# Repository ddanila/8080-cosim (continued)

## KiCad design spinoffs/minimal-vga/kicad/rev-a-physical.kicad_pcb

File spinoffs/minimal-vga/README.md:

# VJUGA minimal-VGA experiment

Status: **EXPERIMENTAL, WITH TWO PHYSICAL TRACKS**.

VJUGA explores a smaller +5 V, Z80-based board with socketed ROM, one 64 KiB
4164-style DRAM bank, keyboard I/O, and a VGA-oriented display path. It is an
independent experiment, not the main Juku replica and not a released hardware
product. The monolithic Rev A board remains on design hold. For modular Rev B,
the active order target is a complete five-board first article with VGA and TTL
serial; it remains on order hold while `docs/rev-b-five-board-order-plan.md` is
executed.

## Rev B modular status

[Rev B status](docs/rev-b-status.md) summarizes the five-card system and its
completed desk gates. The [five-board order plan](docs/rev-b-five-board-order-plan.md)
controls release. The [keyboard encoder pinout mismatch](docs/rev-b-io-parts.md#keyboard-pinout-mismatch--release-blocker)
requires correction and I/O package requalification before upload; physical
first-article acceptance remains pending. Use the
[current bench template](docs/rev-b-b1-bench-log.md) after the authorized order
arrives. Use only the exact five-archive candidate identified by the release
record; superseded packages must not be uploaded.

## Rev A monolithic status

### What works

- `sim/boot_check.sh` runs the patched Juku ROM on T80 in Z80 mode and
  compares the framebuffer with cosim after 6,000 video writes. This checks a
  bounded boot workload, not a complete banner, prompt or physical display.
- `sim/vjuga_boot_check.sh` runs the tv80 twin with the shared РУ5 DRAM,
  D6 decode-PROM and D8 pager models from `hdl/devices.v`, using the validated
  PROM tables. Both Mode B (D6 decode) and Mode A (U5's coarse A15/A14 decode)
  match the same bounded framebuffer oracle. This exercises the modeled
  memory path; it does not qualify socketed chips or prove detection of every
  chip fault. D8's output is unused and is not checked by this guard. Mode B
  uses D6 D0/pin12 as active-low `ROM_N`.
- The pinned T80 core also executes a built-in synthetic ROM (smoke test).
- The synthetic test exercises CPU ROM/RAM/I/O cycles, a bit-sliced DRAM
  model, independent refresh, video arbitration, keyboard-style input, and one
  VGA timing frame.
- An eight-instance logical HDL/KiCad model passes structural comparison.
- Nine structural HDL/board-JSON LVS slices pass with mutation controls,
  covering power/clock/reset, decode, CPU/ROM, DRAM bank and muxes, refresh,
  spare socket, timing and PPI. Whole-board coverage remains incomplete;
  these comparisons do not establish routed-copper continuity. See
  [LVS coverage](docs/rev-a-lvs-coverage.md) for exact counts and boundaries.
- U23 is retained only as an empty DNP spare socket. Its eight outputs have no
  consumers and the verified video timing/request handoff is U40/U41; generated
  assembly artifacts therefore omit U23 from owner IC insertion while still
  mounting its routed socket. Stage 7 LVS guards that exact socket topology.
- The Rev A physical source has 119 refs and 133 modeled nets, and now sockets
  the real Juku decode PROMs (U3 К556РТ4, U4 К155РЕ3) with a Mode-A/Mode-B
  jumper plus the Phase 4 observability headers (J96 clock-control, J97 high
  address + write strobe, J98 control bus); `check_rev_a_physical` enforces
  decode-socket and observability contracts that match the verified twin.
- **The framebuffer-readback boot oracle is built and validated.**
  `sim/vjuga_readback_check.sh` boots the twin with `+capture`, reassembles the
  write stream (`tools/vjuga_fb_readback/reassemble.py`), and confirms it equals
  both the twin's own dump and cosim's `vram.bin` at the selected write cutoff
  (default 6000). This validates bounded replay, not completion of the banner
  or physical capture reliability. Bench comparisons require matching ROM,
  cutoff and initial state; see [the procedure](docs/phase4-bench-bringup.md). A twin
  reference trace (`tools/vjuga_single_step/`) backs the UNO single-step rig.
- The committed four-layer routed PCB includes the Phase 3 decode sockets and
  observability headers and passes the repository's KiCad DRC and
  unconnected-item checks. Independent schematic/copper and power-return review
  still holds release.
- Any Rev A fabrication package predates both the U20/U21
  address-mux enable correction and the U22 refresh-counter cascade correction,
  and is **stale; do not upload or order it**. Do not confuse it with the separately
  validated Rev B packages under `fab/minimal-vga/revb/package/`. The Rev A upload ZIP is absent from the current workspace;
  [manufacturing readiness](docs/rev-a-manufacturing-readiness.md) owns its release gates.
  A fresh guarded stable-KiCad export and checksum are required.

### CPU and ROM

The Z80 supports the experiment's single +5 V supply. The adapted ROM replaces
three 8080 undocumented NOP opcodes and updates one checksum byte. The boot
gate compares original and patched 8080 framebuffers at its selected write
cutoff, then compares the T80 Z80 result; it does not prove every firmware
service equivalent. See [ROM images](roms/README.md) for the patches, hashes
and reproduction commands. T80 runs in Z80 mode (`Mode => 0`).

### What does not work yet

- The current Rev A copper includes the Phase 3 decode sockets and observability
  headers and passes zero-violation/zero-unconnected KiCad DRC. Its two inner
  layers are reserved for filled GND/VCC planes; independent review remains.
- The U5 decode is simulated in both jumper modes, and U24's DRAM
  timing/wait-state reference passes the slower vendored MK4564-12 limits at
  4 MHz. Neither GAL has been compiled/programmed or validated in hardware.
- The physical U20/U21 mux inputs have CPU A0–A7 and refresh-row outputs,
  without CPU-column or video-address paths. The runnable DRAM scaffold does
  not close that hardware gap; see [the chip map](docs/rev-a-chip-map.md#dram-and-arbitration).
- The VGA test proves timing activity, not a Juku banner or prompt sourced from
  shared DRAM.
- No independent end-to-end schematic/design review has released the copper.

Therefore the fabrication outputs are useful engineering artifacts, but the
board is **not authorized for vendor upload, order, or assembly**.

### Current scope

Included in the experiment:

- socketed DIP Z80, ROM, 8255, programmable logic, and eight 4164-compatible
  DRAM devices;
- +5 V input protection, clock/reset, debug headers, and diagnostics;
- keyboard matrix interface;
- shared CPU/refresh/video DRAM scaffold;
- VGA timing/debug header and pixel-serializer path.

Excluded from Rev A: FDC, external bus, tape/serial/network/mouse interfaces,
historical placement, and the original composite/RF chain.

## Evidence map

- `docs/workbench-plan.md`: the bench-fixture direction (test the real Juku
  РУ5/РТ4/РЕ3 parts) and the phased build plan.
- `docs/phase4-bench-bringup.md`: the detailed Phase 4 plan — pre-fab
  observability design-ins, analyzer channel maps, the framebuffer-readback
  boot oracle, the UNO single-step rig, and the assembly/chip-test ladder.
- `hdl/README.md`: exactly what the synthetic simulation proves.
- `docs/rev-a-chip-map.md`: current physical decomposition.
- `docs/rev-a-gal-equations.md`: unvalidated programmable-logic draft.
- `docs/rev-a-placement-rules.md`: placement policy.
- `docs/rev-a-power-budget.md`: conservative planning estimate.
- `docs/rev-a-sourcing-plan.md`: future sourcing/assembly policy; stock must be
  rechecked at order time.
- `docs/rev-a-drc-readiness.md`: current stable-KiCad full-DRC result
  bound to the exact source-board SHA; the former fabrication package is
  explicitly stale after the mux-enable and refresh-counter corrections.
- `docs/rev-a-lvs-coverage.md`: exact staged physical-LVS scope, negative
  control, and the groups still outside the whole-board comparison.
- `docs/rev-a-usb-c-candidate.md`: checksum- and geometry-guarded exact HRO
  TYPE-C-31-M-17/C283540 J3 candidate; order-time orientation/stock remains.
- `docs/rev-a-ptc-candidate.md`: checksum-, electrical-, topology-, and
  static-fit-guarded Bourns MF-RG300-0-14/C3761779 F1 candidate; thermal,
  stock, and first-article checks remain.
- `docs/rev-a-tvs-candidate.md`: checksum-, polarity-, topology-, geometry-,
  and routed-clearance-guarded Littelfuse P4KE6.8A-B/C1666224 D1 candidate;
  surge, stock, and first-article checks remain.
- `kicad/fab-notes.md`: routed/package facts and release blockers.
- `docs/rev-a-manufacturing-readiness.md`: top-level package/design status.
- `external/`: pinned-core and third-party design notes.

Generated reports under `fab/minimal-vga/` are ignored build artifacts. Their
individual `READY` labels mean the named mechanical/package check passed; they
do not override the top-level design hold.

## Checks

Run the current simulation and structural/physical checks:

```sh
spinoffs/minimal-vga/sim/check.sh
```

Run only the logical schematic/HDL comparison:

```sh
spinoffs/minimal-vga/sync/check.sh
```

Run the completed physical-board LVS stages:

```sh
spinoffs/minimal-vga/sync/rev_a_power_clock_reset_lvs.sh
spinoffs/minimal-vga/sync/rev_a_decode_lvs.sh
spinoffs/minimal-vga/sync/rev_a_cpu_rom_lvs.sh
spinoffs/minimal-vga/sync/rev_a_dram_bank_lvs.sh
spinoffs/minimal-vga/sync/rev_a_dram_mux_lvs.sh
spinoffs/minimal-vga/sync/rev_a_refresh_counter_lvs.sh
spinoffs/minimal-vga/sync/rev_a_spare_socket_lvs.sh
spinoffs/minimal-vga/sync/rev_a_dram_timing_lvs.sh
spinoffs/minimal-vga/sync/rev_a_ppi_lvs.sh
```

Regenerate fabrication review artifacts only after accepting that they remain
non-release outputs:

```sh
spinoffs/minimal-vga/kicad/export_fab.sh
```

## Rev A release gate

This gate applies to the monolithic Rev A bench fixture. The modular Rev B
order criteria are in the [five-board order plan](docs/rev-b-five-board-order-plan.md).

Established simulation evidence:

- `sim/boot_check.sh` matches the cosim framebuffer at 6000 video writes.
- `sim/vjuga_boot_check.sh` matches both jumper modes through the Rev A top
  using the РУ5 DRAM and РТ4 decode models; the instantiated РЕ3 output is
  unused and unchecked.
- Decode and U24 DRAM-timing equations are simulated; see
  `sim/u24_dram_timing_check.sh`.

VGA output is waived for Rev A's bench-fixture scope: the guarded framebuffer
capture is its bounded boot oracle for the РУ5/РТ4 memory path. РЕ3 testing
requires a separate output-table capture from the debug header, as described
in the [bench procedure](docs/phase4-bench-bringup.md). This waiver does not
apply to the five-board Rev B order target.

Before Rev A can become an order candidate:

1. Complete the physical DRAM addressing and resolve its scanout scope under
   [the manufacturing requirements](docs/rev-a-manufacturing-readiness.md#remaining-release-requirements).
2. Compile, program and review the equations on the exact chosen GAL22V10
   devices.
3. Validate DRAM, reset, clock, power, connector and socket pinouts against
   selected parts.
4. Obtain an independent schematic, copper, Gerber, drill and power-return
   review, plus full-board LVS or an explicit owner waiver naming that
   independent review as compensating evidence.
5. Regenerate all package artifacts after the design is frozen.

Until then, work on VJUGA must not distract from the main replica's P0 closure
items in the repository-root `PLAN.md`.

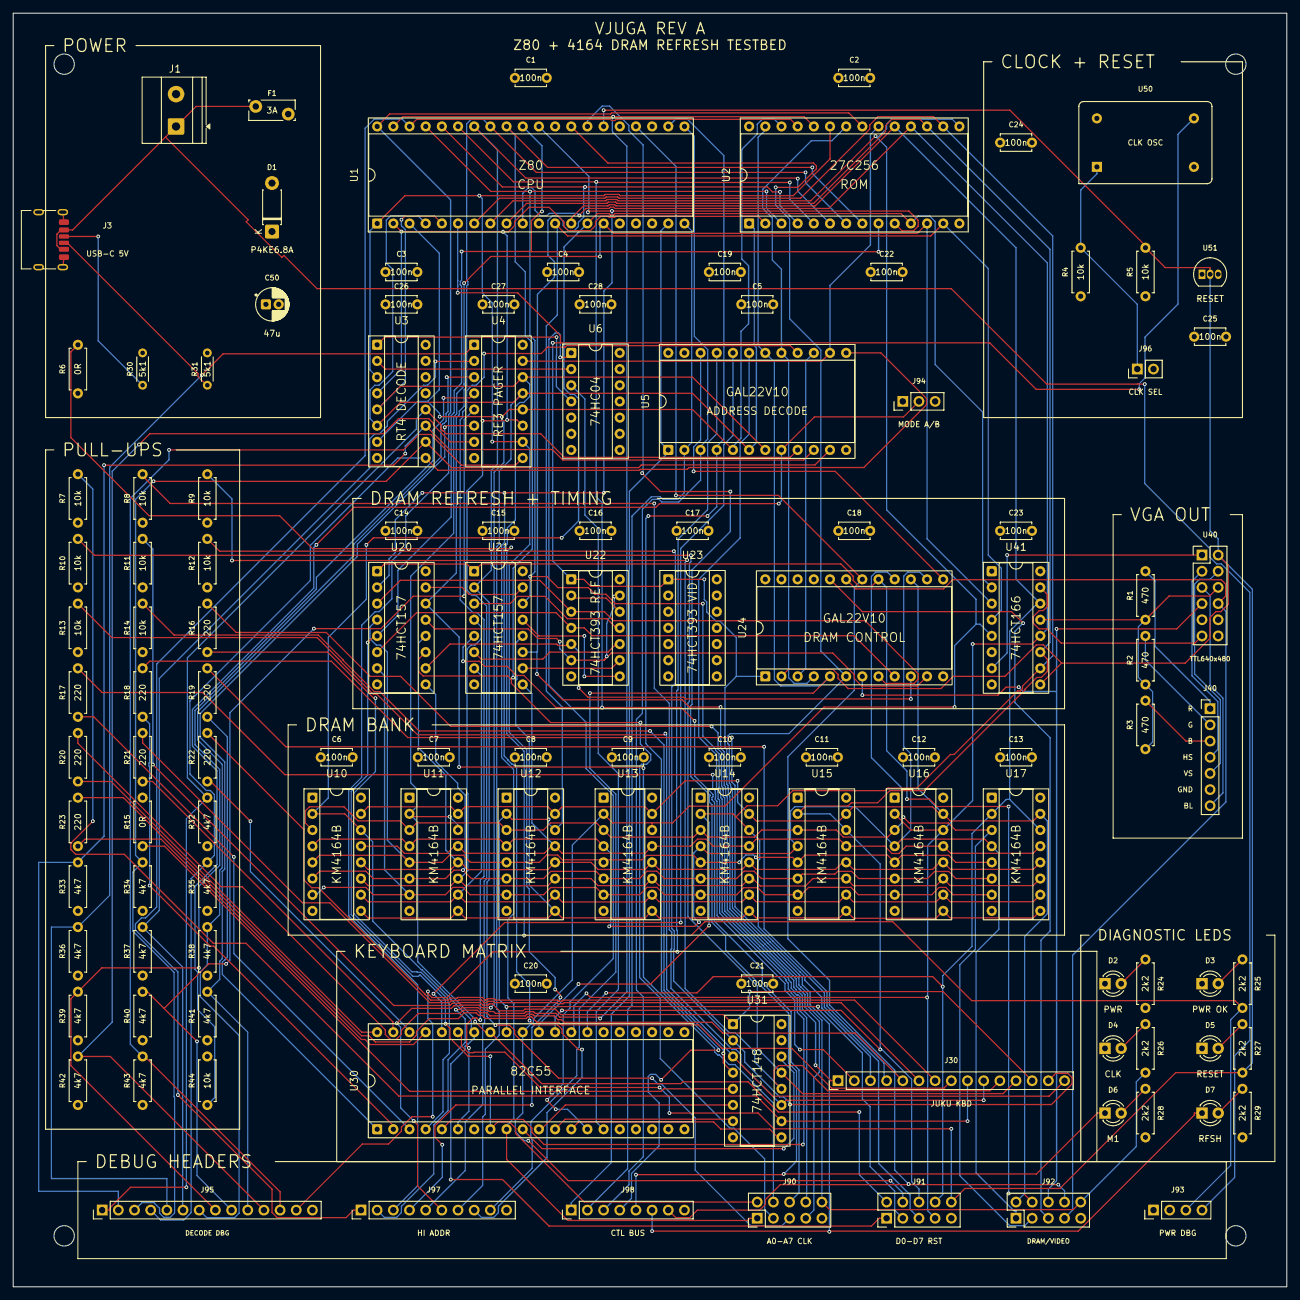
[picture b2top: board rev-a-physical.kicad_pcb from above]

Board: 4 copper layers, 200.0 x 200.0 mm, 119 parts (0 on the bottom side), 133 nets.

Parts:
C1, C2, C3, C4, C5, C6, C7, C8, C9, C10, C11, C12, C13, C14, C15, C16, C17, C18, C19, C20, C21, C22, C23, C24, C25, C26, C27, C28: 100n; C_Disc_D4.7mm_W2.5mm_P5.00mm
C50: 47u; CP_Radial_D5.0mm_P2.00mm
D1: P4KE6.8A; D_DO-41_SOD81_P7.62mm_Horizontal
D2: PWR; LED_D3.0mm
D3: PWR OK; LED_D3.0mm
D4: CLK; LED_D3.0mm
D5: RESET; LED_D3.0mm
D6: M1; LED_D3.0mm
D7: RFSH; LED_D3.0mm
F1: 3A; Fuse_Bourns_MF-RG300
J1: 5V_IN; TerminalBlock_Phoenix_MKDS-1,5-2-5.08_1x02_P5.08mm_Horizont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
J3: USB-C 5V; USB_C_Receptacle_HRO_TYPE-C-31-M-17
J30: JUKU KBD; PinHeader_1x15_P2.54mm_Vertical
J40: VGA_HEADER; PinHeader_1x07_P2.54mm_Vertical
J90: A0-A7 CLK; PinHeader_2x05_P2.54mm_Vertical
J91: D0-D7 RST; PinHeader_2x05_P2.54mm_Vertical
J92: DRAM/VIDEO; PinHeader_2x05_P2.54mm_Vertical
J93: PWR DBG; PinHeader_1x04_P2.54mm_Vertical
J94: MODE A/B; PinHeader_1x03_P2.54mm_Vertical
J95: DECODE DBG; PinHeader_1x14_P2.54mm_Vertical
J96: CLK SEL; PinHeader_1x02_P2.54mm_Vertical
J97: HI ADDR; PinHeader_1x10_P2.54mm_Vertical
J98: CTL BUS; PinHeader_1x08_P2.54mm_Vertical
R1, R2, R3: 470; R_Axial_DIN0207_L6.3mm_D2.5mm_P7.62mm_Horizontal
R4, R5, R7, R8, R9, R10, R11, R12, R13, R14, R44: 10k; R_Axial_DIN0207_L6.3mm_D2.5mm_P7.62mm_Horizontal
R6, R15: 0R; R_Axial_DIN0207_L6.3mm_D2.5mm_P7.62mm_Horizontal
R16, R17, R18, R19, R20, R21, R22, R23: 220; R_Axial_DIN0207_L6.3mm_D2.5mm_P7.62mm_Horizontal
R24, R25, R26, R27, R28, R29: 2k2; R_Axial_DIN0207_L6.3mm_D2.5mm_P7.62mm_Horizontal
R30, R31: 5k1; R_Axial_DIN0204_L3.6mm_D1.6mm_P5.08mm_Horizontal
R32, R33, R34, R35, R36, R37, R38, R39, R40, R41, R42, R43: 4k7; R_Axial_DIN0207_L6.3mm_D2.5mm_P7.62mm_Horizontal
U1: Z80; DIP-40_W15.24mm_Socket
U2: 27C256; DIP-28_W15.24mm_Socket
U3: RT4 DECODE; DIP-16_W7.62mm_Socket
U4: RE3 PAGER; DIP-16_W7.62mm_Socket
U5, U24: GAL22V10; DIP-24_W15.24mm_Socket
U6: 74HC04; DIP-14_W7.62mm_Socket
U10, U11, U12, U13, U14, U15, U16, U17: KM4164B; DIP-16_W7.62mm_Socket
U20, U21: 74HCT157; DIP-16_W7.62mm_Socket
U22: 74HCT393 REF; DIP-14_W7.62mm_Socket
U23: 74HCT393 VID; DIP-14_W7.62mm_Socket
U30: 82C55; DIP-40_W15.24mm_Socket
U31: 74HCT148; DIP-16_W7.62mm_Socket
U40: TTL640x480; PinHeader_2x06_P2.54mm_Vertical
U41: 74HCT166; DIP-16_W7.62mm_Socket
U50: CLK OSC; Oscillator_DIP-14
U51: RESET; TO-92_Inline

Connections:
A0: J90.1, U1.30, U2.10, U20.2, U30.9
A1: J90.2, U1.31, U2.9, U20.5, U30.8
A2: J90.3, U1.32, U2.8, U20.11
A3: J90.4, U1.33, U2.7, U20.14
A4: J90.5, U1.34, U2.6, U21.2
A5: J90.6, U1.35, U2.5, U21.5
A6: J90.7, U1.36, U2.4, U21.11
A7: J90.8, U1.37, U2.3, U21.14
A8: J97.1, U1.38, U2.25
A9: J97.2, U1.39, U2.24
A10: J97.3, U1.40, U2.21
A11: J97.4, U1.1, U2.23, U3.3, U4.10
A12: J97.5, U1.2, U2.2, U3.4, U4.11
A13: J97.6, U1.3, U2.26, U3.7, U4.12, U5.5
A14: J97.7, U1.4, U2.1, U3.6, U4.13, U5.6
A15: J97.8, U1.5, U3.5, U4.14, U5.7
ADDRMUX_SEL: J92.4, U20.1, U21.1, U24.17
BLANK_N: J40.7, U40.5
CAS_N: J92.2, U10.15, U11.15, U12.15, U13.15, U14.15, U15.15, U16.15, U17.15, U24.15
CLK: J90.10, J92.10, R26.1, U1.6, U22.1, U23.1, U24.1, U50.8
D0: J91.1, U1.14, U2.11, U10.2, U10.14, U30.34, U41.2
D1: J91.2, U1.15, U2.12, U11.2, U11.14, U30.33, U41.3
D2: J91.3, U1.12, U2.13, U12.2, U12.14, U30.32, U41.4
D3: J91.4, U1.8, U2.15, U13.2, U13.14, U30.31, U41.5
D4: J91.5, U1.7, U2.16, U14.2, U14.14, U30.30, U41.10
D5: J91.6, U1.9, U2.17, U15.2, U15.14, U30.29, U41.11
D6: J91.7, U1.10, U2.18, U16.2, U16.14, U30.28, U41.12
D7: J91.8, U1.13, U2.19, U17.2, U17.14, U30.27, U41.14
DECODE_WAIT_N: U5.22, U24.13
DEC_RAM_N: J95.2, R33.2, U3.11, U5.10
DEC_REV: J95.3, R34.2, U3.10, U5.11
DEC_ROE_N: J95.4, R35.2, U3.9, U5.13
DEC_ROM_N: J95.1, R32.2, U3.12, U5.9
DRAM_A0: U10.5, U11.5, U12.5, U13.5, U14.5, U15.5, U16.5, U17.5, U20.4
DRAM_A1: U10.7, U11.7, U12.7, U13.7, U14.7, U15.7, U16.7, U17.7, U20.7
DRAM_A2: U10.6, U11.6, U12.6, U13.6, U14.6, U15.6, U16.6, U17.6, U20.9
DRAM_A3: U10.12, U11.12, U12.12, U13.12, U14.12, U15.12, U16.12, U17.12, U20.12
DRAM_A4: U10.11, U11.11, U12.11, U13.11, U14.11, U15.11, U16.11, U17.11, U21.4
DRAM_A5: U10.10, U11.10, U12.10, U13.10, U14.10, U15.10, U16.10, U17.10, U21.7
DRAM_A6: U10.13, U11.13, U12.13, U13.13, U14.13, U15.13, U16.13, U17.13, U21.9
DRAM_A7: U10.9, U11.9, U12.9, U13.9, U14.9, U15.9, U16.9, U17.9, U21.12
DRAM_WE_N: J92.3, U10.3, U11.3, U12.3, U13.3, U14.3, U15.3, U16.3, U17.3, U24.16
GND: C1.2, C2.2, C3.2, C4.2, C5.2, C6.2, C7.2, C8.2, C9.2, C10.2, C11.2, C12.2, C13.2, C14.2, C15.2, C16.2, C17.2, C18.2, C19.2, C20.2, C21.2, C22.2, C23.2, C24.2, C25.2, C26.2, C27.2, C28.2, C50.2, D1.2, D2.1, D3.1, D4.1, D5.1, J1.2, J3.A12, J3.B12, J3.SH, J40.6, J90.9, J91.9, J92.9, J93.2, J94.3, J95.14, J96.2, J97.10, J98.8, R15.2, R30.2, R31.2, R44.2, U1.29, U2.14, U3.8, U3.13, U3.14, U3.15, U4.8, U5.12, U6.5, U6.7, U6.9, U6.11, U6.13, U10.16, U11.16, U12.16, U13.16, U14.16, U15.16, U16.16, U17.16, U20.8, U20.15, U21.8, U21.15, U22.2, U22.7, U22.12, U23.2, U23.7, U23.12, U23.13, U24.12, U30.7, U31.8, U40.10, U40.12, U41.1, U41.6, U41.8, U50.7, U51.1
HSYNC_N: J40.4, U40.3
IORQ_N: J98.2, U1.20, U5.2
IO_RD_N: U5.19, U30.5
IO_WR_N: U5.20, U30.36
KBD_COL0: J30.1, R16.2
KBD_COL0_DRV: R16.1, U30.4
KBD_COL1: J30.2, R17.2
KBD_COL1_DRV: R17.1, U30.3
KBD_COL2: J30.3, R18.2
KBD_COL2_DRV: R18.1, U30.2
KBD_COL3: J30.4, R19.2
KBD_COL3_DRV: R19.1, U30.1
KBD_COL4: J30.5, R20.2
KBD_COL4_DRV: R20.1, U30.40
KBD_COL5: J30.6, R21.2
KBD_COL5_DRV: R21.1, U30.39
KBD_COL6: J30.7, R22.2
KBD_COL6_DRV: R22.1, U30.38
KBD_COL7: J30.8, R23.2
KBD_COL7_DRV: R23.1, U30.37
KBD_EN_N: R15.1, U31.5
KBD_GS_N: U30.10, U31.14
KBD_ROW0_N: J30.9, R7.2, U31.10
KBD_ROW1_N: J30.10, R8.2, U31.11
KBD_ROW2_N: J30.11, R9.2, U31.12
KBD_ROW3_N: J30.12, R10.2, U31.13
KBD_ROW4_N: J30.13, R11.2, U31.1
KBD_ROW5_N: J30.14, R12.2, U31.2
KBD_ROW6_N: J30.15, R13.2, U31.3
KBD_ROW7_N: R14.2, U31.4
KBD_ROW_A0_N: U30.13, U31.9
KBD_ROW_A1_N: U30.12, U31.7
KBD_ROW_A2_N: U30.11, U31.6
LED_CLK_A: D4.2, R26.2
LED_M1_A: D6.2, R28.2
LED_PWR_A: D2.2, R24.2
LED_PWR_OK_A: D3.2, R25.2
LED_RESET_A: D5.2, R27.2
LED_RFSH_A: D7.2, R29.2
M1_N: D6.1, J98.5, U1.27
MEM_RD_N: U2.22, U5.17, U24.4
MEM_WR_N: J97.9, U2.27, U5.18, U24.5
MODE_B: J94.2, R44.1, U5.8
MREQ_N: J98.1, U1.19, U5.1
OSC_OE_N: J96.1, R4.2, U50.1
PC0: U6.1, U30.14
PC0_N: U3.2, U6.2
PC1: U6.3, U30.15
PC1_N: U3.1, U6.4
PIXCLK: U40.1, U41.7
PIXEL: R1.1, R2.1, R3.1, U40.6, U41.13
PIX_LOAD_N: U40.11, U41.15
PPI_CS_N: U5.16, U30.6
PWR_OK: J93.3, R6.2, R25.1
RAM_CE_N: U5.15, U24.3
RAS_N: J92.1, U10.4, U11.4, U12.4, U13.4, U14.4, U15.4, U16.4, U17.4, U24.14
RD_N: J98.3, U1.21, U5.3
RE3_D0: J95.5, R36.2, U4.1
RE3_D1: J95.6, R37.2, U4.2
RE3_D2: J95.7, R38.2, U4.3
RE3_D3: J95.8, R39.2, U4.4
RE3_D4: J95.9, R40.2, U4.5
RE3_D5: J95.10, R41.2, U4.6
RE3_D6: J95.11, R42.2, U4.7
RE3_D7: J95.12, R43.2, U4.9
REFRESH_ROW0: U20.3, U22.3, U24.8
REFRESH_ROW1: U20.6, U22.4, U24.9
REFRESH_ROW2: U20.10, U22.5, U24.10
REFRESH_ROW3: U20.13, U22.6, U22.13, U24.11
REFRESH_ROW4: U21.3, U22.11
REFRESH_ROW5: U21.6, U22.10
REFRESH_ROW6: U21.10, U22.9
REFRESH_ROW7: U21.13, U22.8
REFRESH_TICK: J92.5, U24.20
RESET_N: J91.10, R5.2, R27.1, U1.26, U24.2, U30.35, U40.2, U41.9, U51.2
REV_OUT: J95.13, U5.21
RFSH_N: D7.1, J98.6, U1.28, U24.6
ROM_CE_N: U2.20, U4.15, U5.14
USB_CC1: J3.A5, R30.1
USB_CC2: J3.B5, R31.1
VCC: C1.1, C2.1, C3.1, C4.1, C5.1, C6.1, C7.1, C8.1, C9.1, C10.1, C11.1, C12.1, C13.1, C14.1, C15.1, C16.1, C17.1, C18.1, C19.1, C20.1, C21.1, C22.1, C23.1, C24.1, C25.1, C26.1, C27.1, C28.1, C50.1, D1.1, F1.2, J93.1, J94.1, R4.1, R5.1, R6.1, R7.1, R8.1, R9.1, R10.1, R11.1, R12.1, R13.1, R14.1, R24.1, R28.1, R29.1, R32.1, R33.1, R34.1, R35.1, R36.1, R37.1, R38.1, R39.1, R40.1, R41.1, R42.1, R43.1, U1.11, U1.16, U1.17, U1.25, U2.28, U3.16, U4.16, U5.24, U6.14, U10.8, U11.8, U12.8, U13.8, U14.8, U15.8, U16.8, U17.8, U20.16, U21.16, U22.14, U23.14, U24.24, U30.26, U31.16, U40.9, U41.16, U50.14, U51.3
VCC_RAW: F1.1, J1.1, J3.A9, J3.B9, J93.4
VGA_B: J40.3, R3.2
VGA_G: J40.2, R2.2
VGA_R: J40.1, R1.2
VIDEO_ACK: J92.7, U24.19, U40.8
VIDEO_REQ: J92.6, U24.7, U40.7
VSYNC_N: J40.5, U40.4
WAIT_N: J92.8, J98.7, U1.24, U24.18
WR_N: J98.4, U1.22, U5.4

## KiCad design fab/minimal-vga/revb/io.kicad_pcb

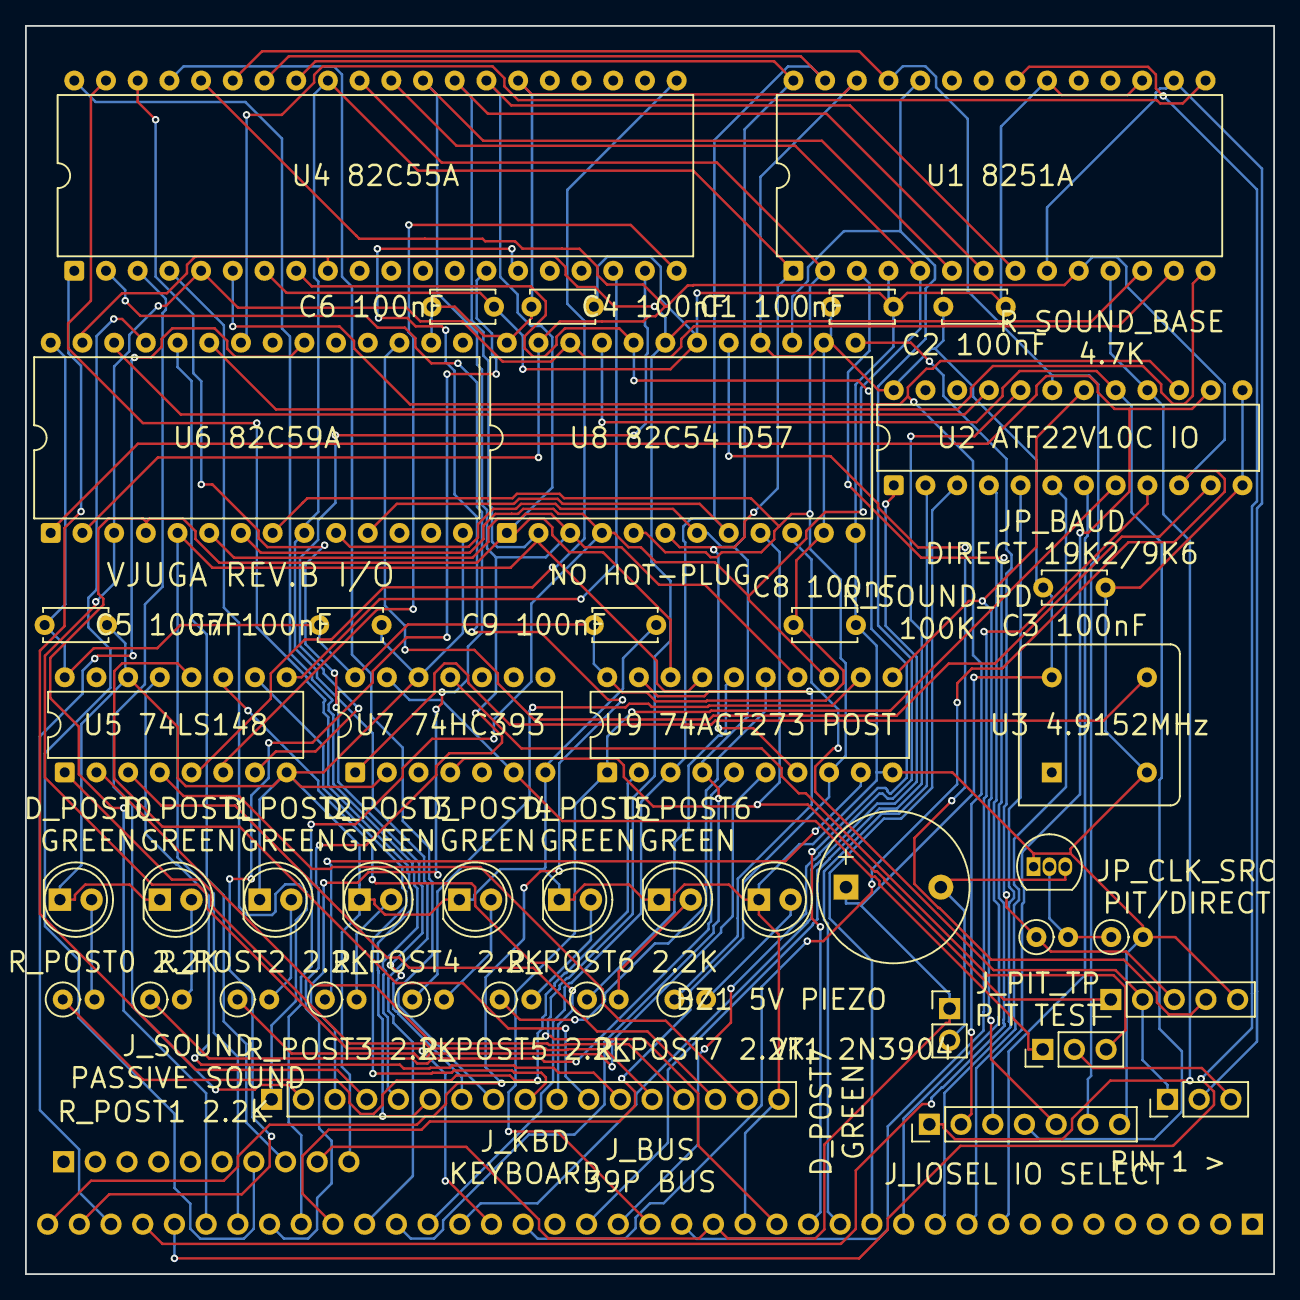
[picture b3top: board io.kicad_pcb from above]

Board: 2 copper layers, 100.0 x 100.0 mm, 46 parts (1 on the bottom side), 89 nets.

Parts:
BZ1: CPT-1207-5LTH-T; Buzzer_12x9.5RM7.6
C1, C2, C3, C4, C5, C6, C7, C8, C9: 100nF; C_Disc_D5.0mm_W2.5mm_P5.00mm
D_POST0, D_POST1, D_POST2, D_POST3, D_POST4, D_POST5, D_POST6, D_POST7: WP710A10LGD; LED_D5.0mm
JP_BAUD: DIRECT 19K2/9K6; PinHeader_1x03_P2.54mm_Vertical
JP_CLK_SRC: PIT/DIRECT; PinHeader_1x03_P2.54mm_Vertical
J_BUS: 39P BUS; PinHeader_1x39_P2.54mm_Horizontal
J_EXT: 10P EXT; PinHeader_1x10_P2.54mm_Horizontal
J_IOSEL: IO SELECT; PinHeader_1x07_P2.54mm_Vertical
J_KBD: KEYBOARD; PinHeader_1x17_P2.54mm_Vertical
J_PIT_TP: PIT TEST; PinHeader_1x05_P2.54mm_Vertical
J_SOUND: PASSIVE SOUND; PinHeader_1x02_P2.54mm_Vertical
Q1: P2N3904ABU; TO-92_Inline
R_POST0, R_POST1, R_POST2, R_POST3, R_POST4, R_POST5, R_POST6, R_POST7: 2.2K; R_Axial_DIN0207_L6.3mm_D2.5mm_P2.54mm_Vertical
R_SOUND_BASE: 4.7K; R_Axial_DIN0207_L6.3mm_D2.5mm_P2.54mm_Vertical
R_SOUND_PD: 100K; R_Axial_DIN0207_L6.3mm_D2.5mm_P2.54mm_Vertical
U1: MD8251A/B; DIP-28_W15.24mm
U2: ATF22V10C IO; DIP-24_W7.62mm
U3: 4.9152MHz; Oscillator_DIP-8
U4: MD82C55A/B; DIP-40_W15.24mm
U5: SN74LS148N; DIP-16_W7.62mm
U6: MD82C59A/B; DIP-28_W15.24mm
U7: 74HC393; DIP-14_W7.62mm
U8: ID82C54 D57; DIP-24_W15.24mm
U9: CD74ACT273E POST; DIP-20_W7.62mm

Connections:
A0: J_BUS.16, U1.12, U4.9, U6.27, U8.19
A1: J_BUS.15, U4.8, U8.20
A2: J_BUS.14, U2.2
A3: J_BUS.13, U2.3
A4: J_BUS.12, U2.4
A5: J_BUS.11, U2.5
A6: J_BUS.10, U2.6
A7: J_BUS.9, U2.7
BAUDCLK: JP_CLK_SRC.2, U1.9, U1.16
BAUD_9600: JP_BAUD.3, U7.11
BAUD_19200: JP_BAUD.1, U7.6, U7.13
BAUD_DIRECT: JP_BAUD.2, JP_CLK_SRC.3
BAUD_MASTER: U3.5, U7.1
CLK: J_BUS.21, U1.24, U8.15
D0: J_BUS.27, U1.27, U4.34, U6.11, U8.8, U9.3
D1: J_BUS.28, U1.28, U4.33, U6.10, U8.7, U9.4
D2: J_BUS.29, U1.1, U4.32, U6.9, U8.6, U9.7
D3: J_BUS.30, U1.2, U4.31, U6.8, U8.5, U9.8
D4: J_BUS.31, U1.5, U4.30, U6.7, U8.4, U9.13
D5: J_BUS.32, U1.6, U4.29, U6.6, U8.3, U9.14
D6: J_BUS.33, U1.7, U4.28, U6.5, U8.2, U9.17
D7: J_BUS.34, U1.8, U4.27, U6.4, U8.1, U9.18
FRAME_TICK: J_BUS.37, U6.20
GND: C1.2, C2.2, C3.2, C4.2, C5.2, C6.2, C7.2, C8.2, C9.2, D_POST0.1, D_POST1.1, D_POST2.1, D_POST3.1, D_POST4.1, D_POST5.1, D_POST6.1, D_POST7.1, J_BUS.17, J_EXT.10, J_IOSEL.7, J_KBD.17, J_PIT_TP.5, Q1.1, R_SOUND_PD.2, U1.4, U1.17, U1.20, U2.12, U2.13, U3.4, U4.7, U5.8, U5.14, U6.14, U7.2, U7.7, U7.12, U8.12, U8.18, U9.10
INTA_N: U2.21, U6.26
INT_N: J_BUS.22, U2.20
IORQ_N: J_BUS.26, U2.1
IO_RESET: J_IOSEL.6, U1.25, U2.19, U4.35
IRQ_A: J_EXT.7, U6.25
IRQ_B: J_EXT.8, U6.24
KBD_COL0: J_KBD.1, U4.4
KBD_COL1: J_KBD.2, U4.3
KBD_COL2: J_KBD.3, U4.2
KBD_COL3: J_KBD.4, U4.1
KBD_COL4: J_KBD.5, U4.40
KBD_COL5: J_KBD.6, U4.39
KBD_COL6: J_KBD.7, U4.38
KBD_COL7: J_KBD.8, U4.37
KBD_ENC0: U4.18, U5.9
KBD_ENC1: U4.19, U5.7
KBD_ENC2: U4.20, U5.6
KBD_ENC_GS: U4.21, U5.5
KBD_ROW0: J_KBD.9, U5.10
KBD_ROW1: J_KBD.10, U5.11
KBD_ROW2: J_KBD.11, U5.12
KBD_ROW3: J_KBD.12, U5.13
KBD_ROW4: J_KBD.13, U5.1
KBD_ROW5: J_KBD.14, U5.2
KBD_ROW6: J_KBD.15, U5.3
KBD_ROW7: J_KBD.16, U5.4
M1_N: J_BUS.19, U2.9
MODE0: J_BUS.38, U4.14
MODE1: J_BUS.39, U4.15
PIC_CS_N: J_IOSEL.3, U2.14, U6.1
PIC_INT: U2.11, U6.17
PIT_BAUD: JP_CLK_SRC.1, J_PIT_TP.2, U8.10
PIT_CLK0: J_PIT_TP.1, U7.4, U8.9
PIT_CS_N: J_IOSEL.4, U2.17, U8.21
PIT_OUT2_TP: J_PIT_TP.4, U8.17
PIT_SOUND: J_PIT_TP.3, R_SOUND_BASE.1, U8.13
POST_CLK: J_IOSEL.5, U2.18, U9.11
POST_LED0_A: D_POST0.2, R_POST0.2
POST_LED1_A: D_POST1.2, R_POST1.2
POST_LED2_A: D_POST2.2, R_POST2.2
POST_LED3_A: D_POST3.2, R_POST3.2
POST_LED4_A: D_POST4.2, R_POST4.2
POST_LED5_A: D_POST5.2, R_POST5.2
POST_LED6_A: D_POST6.2, R_POST6.2
POST_LED7_A: D_POST7.2, R_POST7.2
POST_Q0: R_POST0.1, U9.2
POST_Q1: R_POST1.1, U9.5
POST_Q2: R_POST2.1, U9.6
POST_Q3: R_POST3.1, U9.9
POST_Q4: R_POST4.1, U9.12
POST_Q5: R_POST5.1, U9.15
POST_Q6: R_POST6.1, U9.16
POST_Q7: R_POST7.1, U9.19
PPI_CS_N: J_IOSEL.2, U2.15, U4.6
RD_N: J_BUS.25, U1.13, U4.5, U6.3, U8.22
RESET_N: J_BUS.20, U2.8, U9.1
RX: J_BUS.36, U1.3
SER_RXRDY: U1.14, U6.23
SER_TXRDY: U1.15, U6.22
SOUND_BASE: Q1.2, R_SOUND_BASE.2, R_SOUND_PD.1
SOUND_LOW: BZ1.2, J_SOUND.2, Q1.3
TX: J_BUS.35, U1.21
UART_CS_N: J_IOSEL.1, U1.11, U2.16
VCC5: BZ1.1, C1.1, C2.1, C3.1, C4.1, C5.1, C6.1, C7.1, C8.1, C9.1, J_BUS.18, J_EXT.9, J_SOUND.1, U1.26, U2.24, U3.8, U4.26, U5.16, U6.16, U6.28, U7.14, U8.11, U8.14, U8.16, U8.24, U9.20
WR_N: J_BUS.24, U1.10, U2.10, U4.36, U6.2, U8.23

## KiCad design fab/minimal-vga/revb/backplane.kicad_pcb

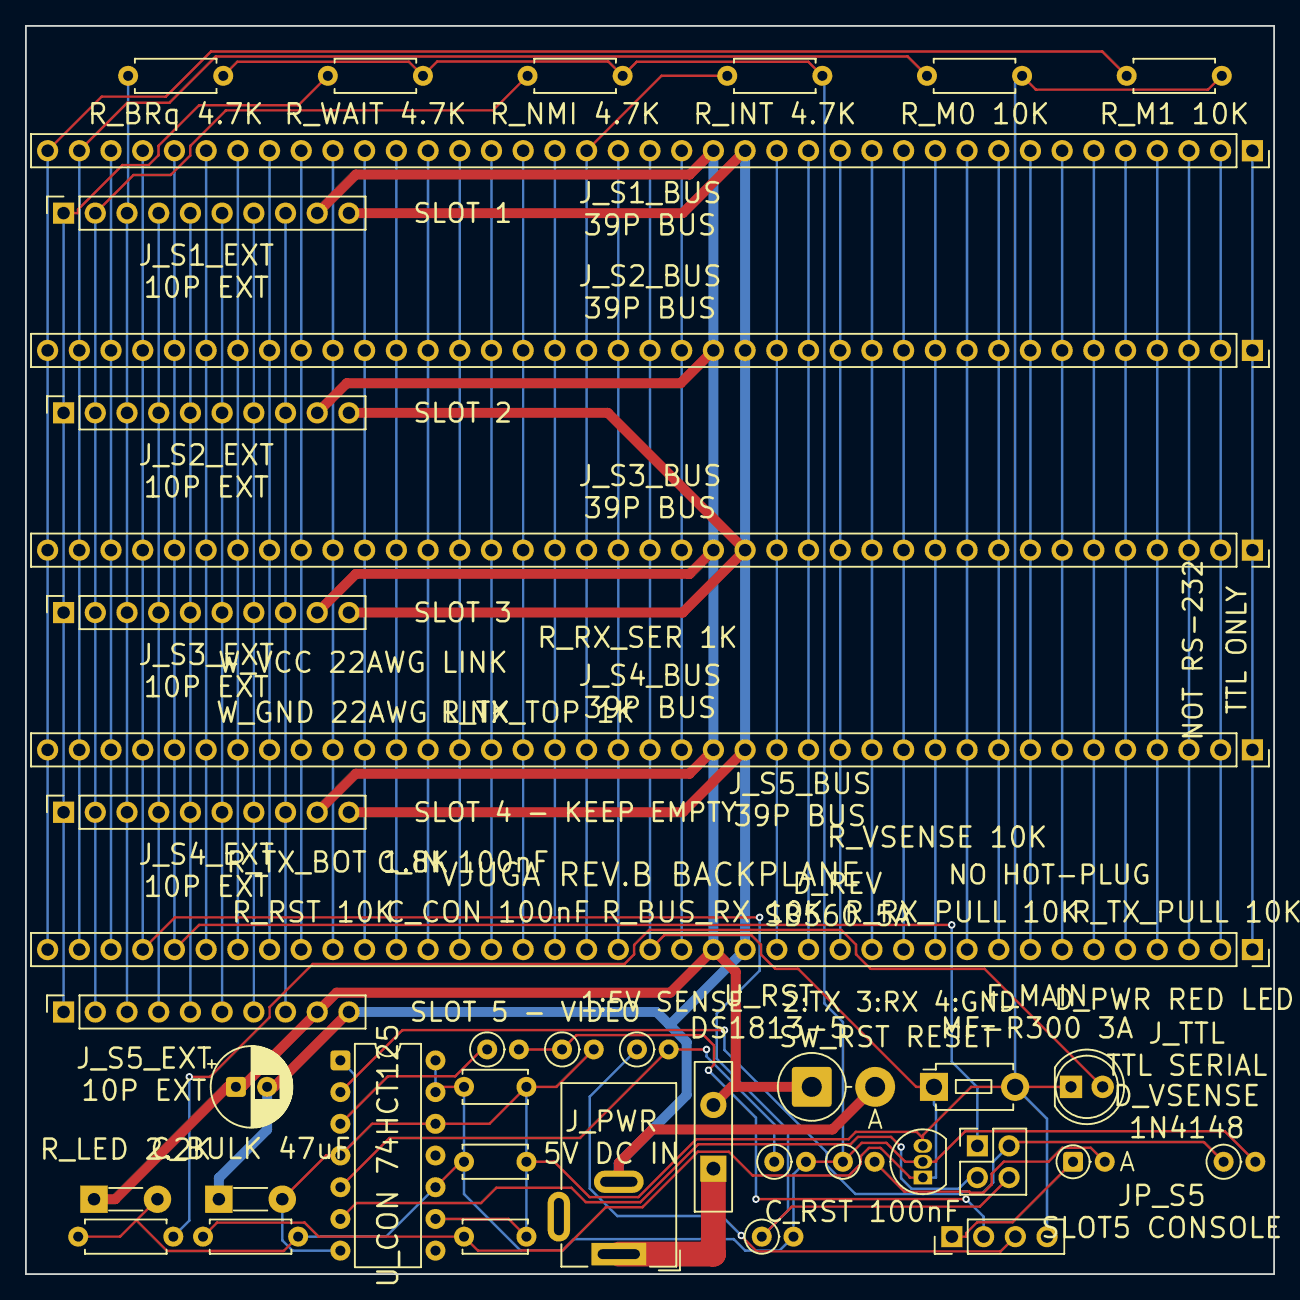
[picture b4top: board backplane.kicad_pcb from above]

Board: 2 copper layers, 100.0 x 100.0 mm, 41 parts (0 on the bottom side), 59 nets.

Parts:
C_BULK: 47uF; CP_Radial_D6.3mm_P2.50mm
C_CON: 100nF; C_Disc_D5.0mm_W2.5mm_P5.00mm
C_IN: 100nF; C_Disc_D5.0mm_W2.5mm_P5.00mm
C_RST: 100nF; C_Disc_D5.0mm_W2.5mm_P5.00mm
D_PWR: RED LED; LED_D5.0mm
D_REV: SB560 5A; D_DO-201AD_P5.08mm_Vertical_AnodeUp
D_VSENSE: 1N4148; D_DO-35_SOD27_P2.54mm_Vertical_AnodeUp
F_MAIN: MF-R300 3A; Fuse_Bourns_MF-R300
JP_S5: SLOT5 CONSOLE; PinHeader_2x02_P2.54mm_Vertical
J_PWR: 5V DC IN; BarrelJack_Wuerth_6941xx301002
J_S1_BUS, J_S2_BUS, J_S3_BUS, J_S4_BUS, J_S5_BUS: 39P BUS; PinSocket_1x39_P2.54mm_Vertical
J_S1_EXT, J_S2_EXT, J_S3_EXT, J_S4_EXT, J_S5_EXT: 10P EXT; PinSocket_1x10_P2.54mm_Vertical
J_TTL: TTL SERIAL; PinHeader_1x04_P2.54mm_Vertical
R_BRQ: 4.7K; R_Axial_DIN0207_L6.3mm_D2.5mm_P7.62mm_Horizontal
R_BUS_RX: 10K; R_Axial_DIN0207_L6.3mm_D2.5mm_P2.54mm_Vertical
R_INT: 4.7K; R_Axial_DIN0207_L6.3mm_D2.5mm_P7.62mm_Horizontal
R_LED: 2.2K; R_Axial_DIN0207_L6.3mm_D2.5mm_P7.62mm_Horizontal
R_M0, R_M1: 10K; R_Axial_DIN0207_L6.3mm_D2.5mm_P7.62mm_Horizontal
R_NMI: 4.7K; R_Axial_DIN0207_L6.3mm_D2.5mm_P7.62mm_Horizontal
R_RST: 10K; R_Axial_DIN0207_L6.3mm_D2.5mm_P7.62mm_Horizontal
R_RX_PULL: 10K; R_Axial_DIN0207_L6.3mm_D2.5mm_P2.54mm_Vertical
R_RX_SER: 1K; R_Axial_DIN0207_L6.3mm_D2.5mm_P2.54mm_Vertical
R_TX_BOT: 1.8K; R_Axial_DIN0207_L6.3mm_D2.5mm_P2.54mm_Vertical
R_TX_PULL: 10K; R_Axial_DIN0207_L6.3mm_D2.5mm_P2.54mm_Vertical
R_TX_TOP: 1K; R_Axial_DIN0207_L6.3mm_D2.5mm_P2.54mm_Vertical
R_VSENSE: 10K; R_Axial_DIN0207_L6.3mm_D2.5mm_P2.54mm_Vertical
R_WAIT: 4.7K; R_Axial_DIN0207_L6.3mm_D2.5mm_P7.62mm_Horizontal
SW_RST: RESET; SW_PUSH_1P1T_6x3.5mm_H4.3_APEM_MJTP1243
U_CON: 74HCT125; DIP-14_W7.62mm
U_RST: DS1813-5; TO-92_Inline
W_GND: 22AWG LINK; WireLink_22AWG_P5.08mm
W_VCC: 22AWG LINK; WireLink_22AWG_P5.08mm

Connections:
A0: J_S1_BUS.16, J_S2_BUS.16, J_S3_BUS.16, J_S4_BUS.16, J_S5_BUS.16
A1: J_S1_BUS.15, J_S2_BUS.15, J_S3_BUS.15, J_S4_BUS.15, J_S5_BUS.15
A2: J_S1_BUS.14, J_S2_BUS.14, J_S3_BUS.14, J_S4_BUS.14, J_S5_BUS.14
A3: J_S1_BUS.13, J_S2_BUS.13, J_S3_BUS.13, J_S4_BUS.13, J_S5_BUS.13
A4: J_S1_BUS.12, J_S2_BUS.12, J_S3_BUS.12, J_S4_BUS.12, J_S5_BUS.12
A5: J_S1_BUS.11, J_S2_BUS.11, J_S3_BUS.11, J_S4_BUS.11, J_S5_BUS.11
A6: J_S1_BUS.10, J_S2_BUS.10, J_S3_BUS.10, J_S4_BUS.10, J_S5_BUS.10
A7: J_S1_BUS.9, J_S2_BUS.9, J_S3_BUS.9, J_S4_BUS.9, J_S5_BUS.9
A8: J_S1_BUS.8, J_S2_BUS.8, J_S3_BUS.8, J_S4_BUS.8, J_S5_BUS.8
A9: J_S1_BUS.7, J_S2_BUS.7, J_S3_BUS.7, J_S4_BUS.7, J_S5_BUS.7
A10: J_S1_BUS.6, J_S2_BUS.6, J_S3_BUS.6, J_S4_BUS.6, J_S5_BUS.6
A11: J_S1_BUS.5, J_S2_BUS.5, J_S3_BUS.5, J_S4_BUS.5, J_S5_BUS.5
A12: J_S1_BUS.4, J_S2_BUS.4, J_S3_BUS.4, J_S4_BUS.4, J_S5_BUS.4
A13: J_S1_BUS.3, J_S2_BUS.3, J_S3_BUS.3, J_S4_BUS.3, J_S5_BUS.3
A14: J_S1_BUS.2, J_S2_BUS.2, J_S3_BUS.2, J_S4_BUS.2, J_S5_BUS.2
A15: J_S1_BUS.1, J_S2_BUS.1, J_S3_BUS.1, J_S4_BUS.1, J_S5_BUS.1
BOARD_RX: J_TTL.3, R_RX_SER.1
BOARD_TX: J_TTL.2, R_TX_BOT.1, R_TX_TOP.2
BUSAK_N: J_S1_EXT.4, J_S2_EXT.4, J_S3_EXT.4, J_S4_EXT.4, J_S5_EXT.4
BUSRQ_N: J_S1_EXT.3, J_S2_EXT.3, J_S3_EXT.3, J_S4_EXT.3, J_S5_EXT.3, R_BRQ.1
CLK: J_S1_BUS.21, J_S2_BUS.21, J_S3_BUS.21, J_S4_BUS.21, J_S5_BUS.21
CON_RX_BUF: R_RX_PULL.1, R_RX_SER.2, U_CON.5
CON_RX_DRIVE: JP_S5.3, U_CON.6
CON_TX_5V: R_TX_TOP.1, U_CON.3
CON_TX_SRC: JP_S5.2, R_TX_PULL.1, U_CON.2
D0: J_S1_BUS.27, J_S2_BUS.27, J_S3_BUS.27, J_S4_BUS.27, J_S5_BUS.27
D1: J_S1_BUS.28, J_S2_BUS.28, J_S3_BUS.28, J_S4_BUS.28, J_S5_BUS.28
D2: J_S1_BUS.29, J_S2_BUS.29, J_S3_BUS.29, J_S4_BUS.29, J_S5_BUS.29
D3: J_S1_BUS.30, J_S2_BUS.30, J_S3_BUS.30, J_S4_BUS.30, J_S5_BUS.30
D4: J_S1_BUS.31, J_S2_BUS.31, J_S3_BUS.31, J_S4_BUS.31, J_S5_BUS.31
D5: J_S1_BUS.32, J_S2_BUS.32, J_S3_BUS.32, J_S4_BUS.32, J_S5_BUS.32
D6: J_S1_BUS.33, J_S2_BUS.33, J_S3_BUS.33, J_S4_BUS.33, J_S5_BUS.33
D7: J_S1_BUS.34, J_S2_BUS.34, J_S3_BUS.34, J_S4_BUS.34, J_S5_BUS.34
FRAME_TICK: J_S1_BUS.37, J_S2_BUS.37, J_S3_BUS.37, J_S4_BUS.37, J_S5_BUS.37
GND: C_CON.2, C_IN.2, C_RST.2, D_PWR.1, J_TTL.4, R_M0.2, R_M1.2, R_TX_BOT.2, SW_RST.2, U_CON.1, U_CON.4, U_CON.7, U_CON.9, U_CON.12, U_RST.3, W_GND.2
GND_BUS: C_BULK.2, D_REV.2, J_PWR.2, J_S1_BUS.17, J_S1_EXT.10, J_S2_BUS.17, J_S2_EXT.10, J_S3_BUS.17, J_S3_EXT.10, J_S4_BUS.17, J_S4_EXT.10, J_S5_BUS.17, J_S5_EXT.10, W_GND.1
HALT_N: J_S1_EXT.6, J_S2_EXT.6, J_S3_EXT.6, J_S4_EXT.6, J_S5_EXT.6
INT_N: J_S1_BUS.22, J_S2_BUS.22, J_S3_BUS.22, J_S4_BUS.22, J_S5_BUS.22, R_INT.1
IORQ_N: J_S1_BUS.26, J_S2_BUS.26, J_S3_BUS.26, J_S4_BUS.26, J_S5_BUS.26
IRQ_A: J_S1_EXT.7, J_S2_EXT.7, J_S3_EXT.7, J_S4_EXT.7, J_S5_EXT.7
IRQ_B: J_S1_EXT.8, J_S2_EXT.8, J_S3_EXT.8, J_S4_EXT.8, J_S5_EXT.8
LED_A: D_PWR.2, R_LED.2
M1_N: J_S1_BUS.19, J_S2_BUS.19, J_S3_BUS.19, J_S4_BUS.19, J_S5_BUS.19
MODE0: J_S1_BUS.38, J_S2_BUS.38, J_S3_BUS.38, J_S4_BUS.38, J_S5_BUS.38, R_M0.1
MODE1: J_S1_BUS.39, J_S2_BUS.39, J_S3_BUS.39, J_S4_BUS.39, J_S5_BUS.39, R_M1.1
MREQ_N: J_S1_BUS.23, J_S2_BUS.23, J_S3_BUS.23, J_S4_BUS.23, J_S5_BUS.23
NMI_N: J_S1_EXT.2, J_S2_EXT.2, J_S3_EXT.2, J_S4_EXT.2, J_S5_EXT.2, R_NMI.1
PWR_RAW: F_MAIN.1, J_PWR.1
RD_N: J_S1_BUS.25, J_S2_BUS.25, J_S3_BUS.25, J_S4_BUS.25, J_S5_BUS.25
RESET_N: C_RST.1, J_S1_BUS.20, J_S2_BUS.20, J_S3_BUS.20, J_S4_BUS.20, J_S5_BUS.20, R_RST.1, SW_RST.1, U_RST.1
RFSH_N: J_S1_EXT.5, J_S2_EXT.5, J_S3_EXT.5, J_S4_EXT.5, J_S5_EXT.5
RX: JP_S5.4, J_S1_BUS.36, J_S2_BUS.36, J_S3_BUS.36, J_S4_BUS.36, J_S5_BUS.36, R_BUS_RX.1
TX: JP_S5.1, J_S1_BUS.35, J_S2_BUS.35, J_S3_BUS.35, J_S4_BUS.35, J_S5_BUS.35
VCC5: C_CON.1, C_IN.1, R_BRQ.2, R_BUS_RX.2, R_INT.2, R_LED.1, R_NMI.2, R_RST.2, R_RX_PULL.2, R_TX_PULL.2, R_VSENSE.1, R_WAIT.2, U_CON.10, U_CON.13, U_CON.14, U_RST.2, W_VCC.2
VCC_BUS: C_BULK.1, D_REV.1, F_MAIN.2, J_S1_BUS.18, J_S1_EXT.9, J_S2_BUS.18, J_S2_EXT.9, J_S3_BUS.18, J_S3_EXT.9, J_S4_BUS.18, J_S4_EXT.9, J_S5_BUS.18, J_S5_EXT.9, W_VCC.1
VCC_SENSE: D_VSENSE.1, J_TTL.1
VSENSE_A: D_VSENSE.2, R_VSENSE.2
WAIT_N: J_S1_EXT.1, J_S2_EXT.1, J_S3_EXT.1, J_S4_EXT.1, J_S5_EXT.1, R_WAIT.1
WR_N: J_S1_BUS.24, J_S2_BUS.24, J_S3_BUS.24, J_S4_BUS.24, J_S5_BUS.24
